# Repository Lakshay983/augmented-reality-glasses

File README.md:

## Ultra 96 Resouces

### Ultra 96 Devboard Schematic
[Schematic](/ultra96-v2-schematics.pdf)

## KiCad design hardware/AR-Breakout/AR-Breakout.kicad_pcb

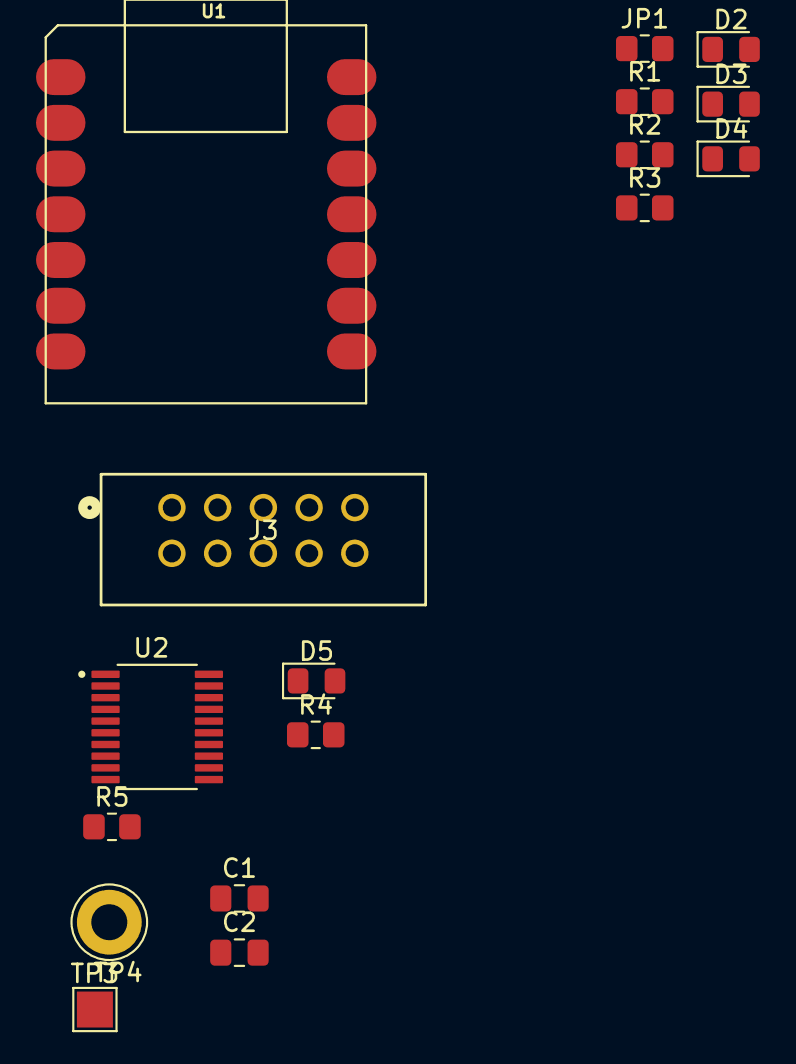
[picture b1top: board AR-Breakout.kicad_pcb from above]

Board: 2 copper layers, 17 parts (0 on the bottom side), 16 nets, no tracks yet.

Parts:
C1, C2: .1uF; C_0805_2012Metric_Pad1.18x1.45mm_HandSolder
D2, D3, D4, D5: LED; LED_0805_2012Metric_Pad1.15x1.40mm_HandSolder
J3: Logic Analyzer; CONN_SFH11-xxxC-D05-ST-XX_SUL
JP1: SolderJumper_2_Open; R_0805_2012Metric_Pad1.20x1.40mm_HandSolder
R1, R2, R3, R4, R5: 1k; R_0805_2012Metric_Pad1.20x1.40mm_HandSolder
TP3: TestPoint; TestPoint_Pad_2.0x2.0mm
TP4: TestPoint; TestPoint_Loop_D3.80mm_Drill2.0mm
U1: SEEEDUINO-XIAO-ESP32C3; MOUDLE14P-SMD-2.54-21X17.8MM
U2: TXS0108EPWR

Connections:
+3.3V: C2.1, U2.19 (VCCB)
/esp32/esp_3V3: JP1.2 (B), R1.1, U1.12 (3V3)
/esp32/esp_5V: R2.1, U1.14 (5V)
/esp32/esp_connected: R4.1, U1.10 (PA5_A9_D9_MISO)
/esp32/esp_heartbeat: R3.1, U1.11 (PA6_A10_D10_MOSI)
/ultra96/uart0_rx: J3.9 (CH1), U1.7 (PB08_A6_D6_TX), U2.18 (B2)
/ultra96/uart0_tx: J3.7 (CH3), U1.8 (PB09_A7_D7_RX), U2.20 (B1)
/ultra96/uart1_rx: J3.10 (CH0), U2.16 (B4)
/ultra96/uart1_tx: J3.8 (CH2), U2.17 (B3)
/ultra96/ultra96_1v8: C1.1, R5.1, TP3.1, U2.2 (VCCA)
GND: C1.2, C2.2, D2.1 (K), D3.1 (K), D4.1 (K), D5.1 (K), J3.1 (GND), U1.13 (GND), U2.11 (GND)
unnamed: D2.2 (A), R1.2
unnamed: D3.2 (A), R2.2
unnamed: D4.2 (A), R3.2
unnamed: D5.2 (A), R4.2
unnamed: R5.2, U2.10 (OE)

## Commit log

2025-09-15 hardware + gitignores
2025-10-08 add hw
2025-10-08 add makefile and files
2025-10-13 made artoolkit submodule and renamed software --> fpga_software and also made a ar_software directory.
2025-10-20 Kill me now :0
2025-10-20 Removed old ARToolkit Submodule
2025-10-20 Removed the old ARToolKit repo and switched to artoolkitx
2025-10-22 fix submodule path on main
2025-10-22 fix submodule path on main (#1)
2025-10-28 add elf file
2025-10-29 add dtb file folder
2025-10-29 wrote script and added requirements.txt
2025-11-03 add dtsi file + rename scripts
2025-11-03 wawa
2025-11-03 wawa weewoo
2025-11-03 wee wee wa woo
2025-11-03 try this
2025-11-26 schem progress
2026-01-04 stuff
2026-01-04 test usb camera
2026-01-04 test usb camera (#2)
2026-01-23 deleted submodule
2026-01-23 add AR_Application software as a repo
2026-01-24 An .xsa file for the ultra96
2026-01-26 deviceTree stuff
2026-01-26 add petalinux built dtb file
2026-01-26 Undid deleted metafile changes and added IP for image passthrough with the TB
2026-01-26 my dtb bricks the board :p
2026-01-26 compile device tree without R5 stuff
2026-01-27 turn IP export zip into folder
2026-01-27 turn IP export zip into folder (#3)
2026-01-27 remove artool kit
2026-01-27 remove artool kit (#4)
2026-01-27 get baseline .bit file
2026-01-28 there is hope where once there was none
2026-01-28 naming scheme + cleanup
2026-01-28 add elf files
2026-01-28 .gitignore comment
2026-01-28 add tested rproc .bit file
2026-01-28 new elf file go brrr
2026-01-28 rename blinky elf file
2026-01-28 flashing R5 script
2026-01-28 read me
2026-01-28 Added System DTBs and Bit files (#5)
    * deviceTree stuff
    * add petalinux built dtb file
    * my dtb bricks the board :p
    * compile device tree without R5 stuff
    * get baseline .bit file
    * naming scheme + cleanup
2026-01-28 R5 blinky (#6)
    * there is hope where once there was none
    * add elf files
    * .gitignore comment
    * new elf file go brrr
    * rename blinky elf file
    * flashing R5 script
2026-01-29 Vivado files zipped, LPD connected with AXI MM2S
2026-02-02 XSA and bitstream, XSA contains bitstream as well
2026-02-02 update dtb instructions
2026-02-02 New changes for the image_passthrough IP
2026-02-02 renamed some dtb files
2026-02-02 add imageIP bit file
2026-02-08 stop tracking folder as normal files
2026-02-09 Stop tracking AR_Application_Software as a normal folder
2026-02-09 Record AR_Application_Software submodule
2026-02-09 dma transfer addresses set for new axi stuff
2026-02-16 continue testing
2026-02-24 Added Vitis Vision submodule
2026-03-18 Added user repo IP -- 16B passthrough block
2026-03-19 system.dtb for display
2026-03-20 test image
2026-03-22 Testing greyscale + gaussian blur
2026-03-23 cv accelerator testing is not going well :( jailcells
2026-03-23 source files
2026-03-23 Accelerators, untested. Please use v2, v1 has undistrotion
2026-03-25 First tb, trying to make gaussian completely match
2026-03-27 Before padding
2026-03-27 Tested accelerator (it finally fricking works)
2026-03-31 Pcb (#7)
    * schem progress
    * stuff
    * PCB
2026-04-02 Accelerator export
2026-04-09 some weird error
2026-04-10 New accelerator
2026-04-10 Frick accelerator
2026-04-10 Hopefully last version
2026-04-10 Missing accelerator parts, I hope
2026-04-11 balls
2026-04-11 idk where these are from but i dont want them to get overwritten
2026-04-12 Accelerator
2026-04-12 Hopefully last verion on this
2026-04-12 Sorry new folder
2026-04-12 add accelerator v4 bit stream
2026-04-12 Accelerator DTB Files (#8)
    * balls
    * balls
    * idk where these are from but i dont want them to get overwritten
    * add accelerator v4 bit stream
    ---------
2026-04-13 Accelerators (#9)
    * Accelerators, untested. Please use v2, v1 has undistrotion
    * First tb, trying to make gaussian completely match
    * Before padding
    * Tested accelerator (it finally fricking works)
    * Accelerator export
    * New accelerator
2026-04-13 Accelerator with larger padding and tlast
2026-04-13 Accelerator for testing tlast and increased padding
2026-04-13 4.1 accelerator bit
2026-04-13 1x1 streaming
2026-04-13 1x1 accelerator pls work I'm begging you
2026-04-13 Added breathing pins ot ctrl
2026-04-13 breathing
2026-04-13 breathing accelerator dtb 4/13/26
2026-04-14 add compile image python script
